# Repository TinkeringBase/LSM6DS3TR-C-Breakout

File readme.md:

[한국어](https://github.com/TinkeringBase/LSM6DS3TR-C-Breakout/blob/main/readme-ko.md)
# TinkeringBase LSM6DS3TR-C IMU breakout
\
Sensor breakout using ST's LSM6DS3TR-C 6DoF IMU, supports Sparkfun Qwiic system.\
While it has low price tag, it provides acceptable performance. So we recommend as entry-level IMU.

## Specification
Supply Voltage (VDD): 1.71~3.6V \
Logic Low (VIL): 0.3\*VDD max \
Logic High (VIH): 0.7\*VDD min \
Current consumption: around 0.9mA at performance mode \
for more information, see [techdata](https://www.st.com/en/mems-and-sensors/lsm6ds3tr-c.html)

## I2C address
the module uses I2C address 0b1101001 (0x6B) by default. to change it to 0b1101000 (0x6A), solder the jumper at the back side of the module.

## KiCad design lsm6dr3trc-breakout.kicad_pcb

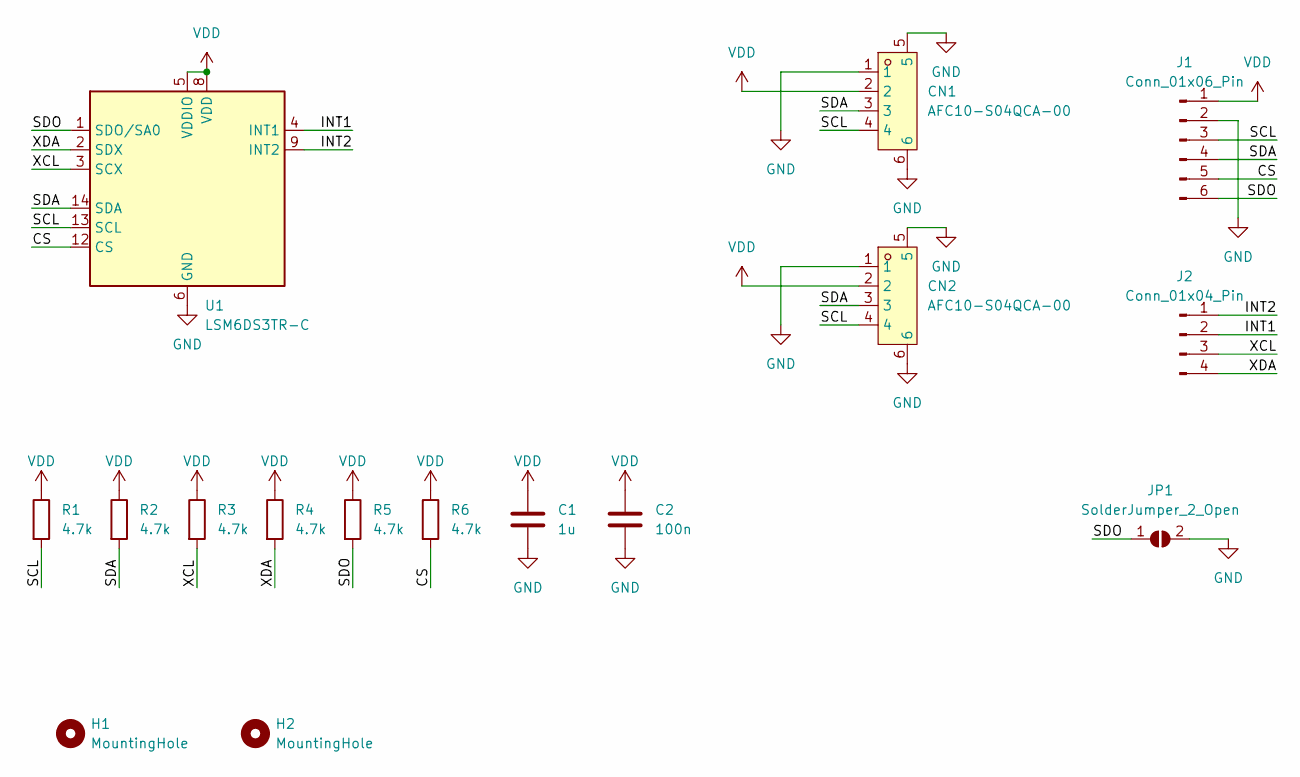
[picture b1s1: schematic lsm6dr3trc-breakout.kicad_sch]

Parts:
C1: 1u; C_0603_1608Metric
C2: 100n; C_0402_1005Metric
CN1, CN2: AFC10-S04QCA-00; CONN-SMD_AFC10-S04QCA-00; LCSC Part C2764183
H1, H2: MountingHole; MountingHole_2.2mm_M2
J1: Conn_01x06_Pin; PinHeader_1x06_P2.54mm_Vertical
J2: Conn_01x04_Pin; PinHeader_1x04_P2.54mm_Vertical
JP1: SolderJumper_2_Open; SolderJumper-2_P1.3mm_Open_TrianglePad1.0x1.5mm
R1, R2, R3, R4, R5, R6: 4.7k; R_0402_1005Metric
U1: LSM6DS3TR-C; LGA-14_3x2.5mm_P0.5mm_LayoutBorder3x4y

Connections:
/CS: J1.5, R6.2, U1.12 (CS)
/INT1: J2.2, U1.4 (INT1)
/INT2: J2.1, U1.9 (INT2)
/SCL: CN1.4, CN2.4, J1.3, R1.2, U1.13 (SCL)
/SDA: CN1.3, CN2.3, J1.4, R2.2, U1.14 (SDA)
/SDO: J1.6, JP1.1 (A), R5.2, U1.1 (SDO/SA0)
/XCL: J2.3, R3.2, U1.3 (SCX)
/XDA: J2.4, R4.2, U1.2 (SDX)
GND: C1.2, C2.2, CN1.1, CN1.5, CN1.6, CN2.1, CN2.5, CN2.6, J1.2, JP1.2 (B), U1.6 (GND), U1.7 (GND)
VDD: C1.1, C2.1, CN1.2, CN2.2, J1.1, R1.1, R2.1, R3.1, R4.1, R5.1, R6.1, U1.5 (VDDIO), U1.8 (VDD)

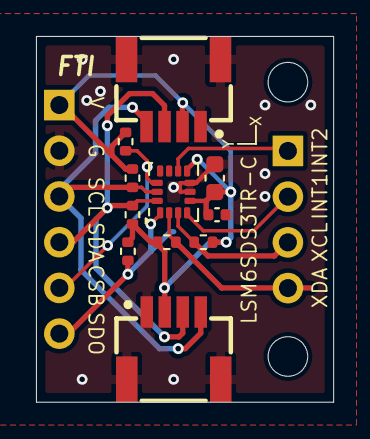
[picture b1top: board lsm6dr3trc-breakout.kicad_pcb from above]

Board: 2 copper layers, 16.5 x 20.3 mm, 16 parts (1 on the bottom side), 10 nets.

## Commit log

2024-04-16 fix qwiic pinout, redo footprint
2024-04-16 highlight external i2c, add readme
2024-04-23 unified IMU footprint
2024-04-23 cleanup
2024-05-10 gitignore
2024-05-19 fix csb resistor, beautify schematic
2024-06-10 fix missing preview
2024-11-26 use lower pullups
2024-12-02 make it dipable
